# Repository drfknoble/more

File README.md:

# My Other Robot for Education (MORE)

## Introduction

Welcome to my repository for my My Other Robot for Education (MORE) project.

<div>

</div>

## Motivation

I started this project after developing my LORE robot (see [http://github.com/DrFKNoble/lore](http://github.com/DrFKNoble/lore)) and seeing how low-cost components affected the robot's performance.

One of the main problems the robot had was that the continuous rotation servo motors I used would start to "drift" after some time (and would need to be manually tuned when they did). So I decided to build a better robot, which used stepper motors instead on servo motors.

## Aims

The aims of this project included:
- Improving upon LORE's performance by using more robust components.
- Developing another mobile robot that, this time, can be used to teach students the principles of mechatronics and robotics.

## Objectives

The objectives of this project included:
- Creating accessible Computer Aided Design (CAD) files.
- Creating accessible Electronics Design Automation (EDA) files.
- Creating accessible source code and software libraries.
- Creating an easy-to-assemble mobile robot that uses an Arduino microcontroller, stepper motors, stepper motor drives, and ultrasonic sensors.

## Repository Structure

The repository is organised as follows:

```console
/MORE      
    /cad                          
        /solidworks                    
        /freecad
        /fabrication
        /renders                     
    /pcb
        /eagle
        /kicad
        /fabrication
    /src
    /doc                      
        /img
        /programming_guide
```

All CAD files can be found in the `/cad` sub-directory. I've included the original SOLIDWORKS files and the open-source equivalents.

All EDA files can be found in the `/pcb` sub-directory. I've included the original Eagle files and the open-source equivalents.

All source code and software libaries are included in the `/src` sub-directory.

Documentation is included in the `/doc` sub-directory.

## Tools Used

I have used the following tools in this project:
- SOLIDWORKS and FreeCAD.
- Eagle and KiCAD.
- Microsoft Visual Studio and Arduino Integrated Development IDE (IDE).

Get FreeCAD here: https://www.freecadweb.org/.  
Get KiCAD here: https://www.kicad.org/.  
Get Arduino IDE here: https://www.arduino.cc/en/software.  
Get Visual Studio here: https://visualstudio.microsoft.com/.  

Alternatively, you can use Microsoft Visual Studio Code as the IDE.

Get Code here: https://code.visualstudio.com/.

## Credit

Dr Frazer K. Noble  
http://drfknoble.com

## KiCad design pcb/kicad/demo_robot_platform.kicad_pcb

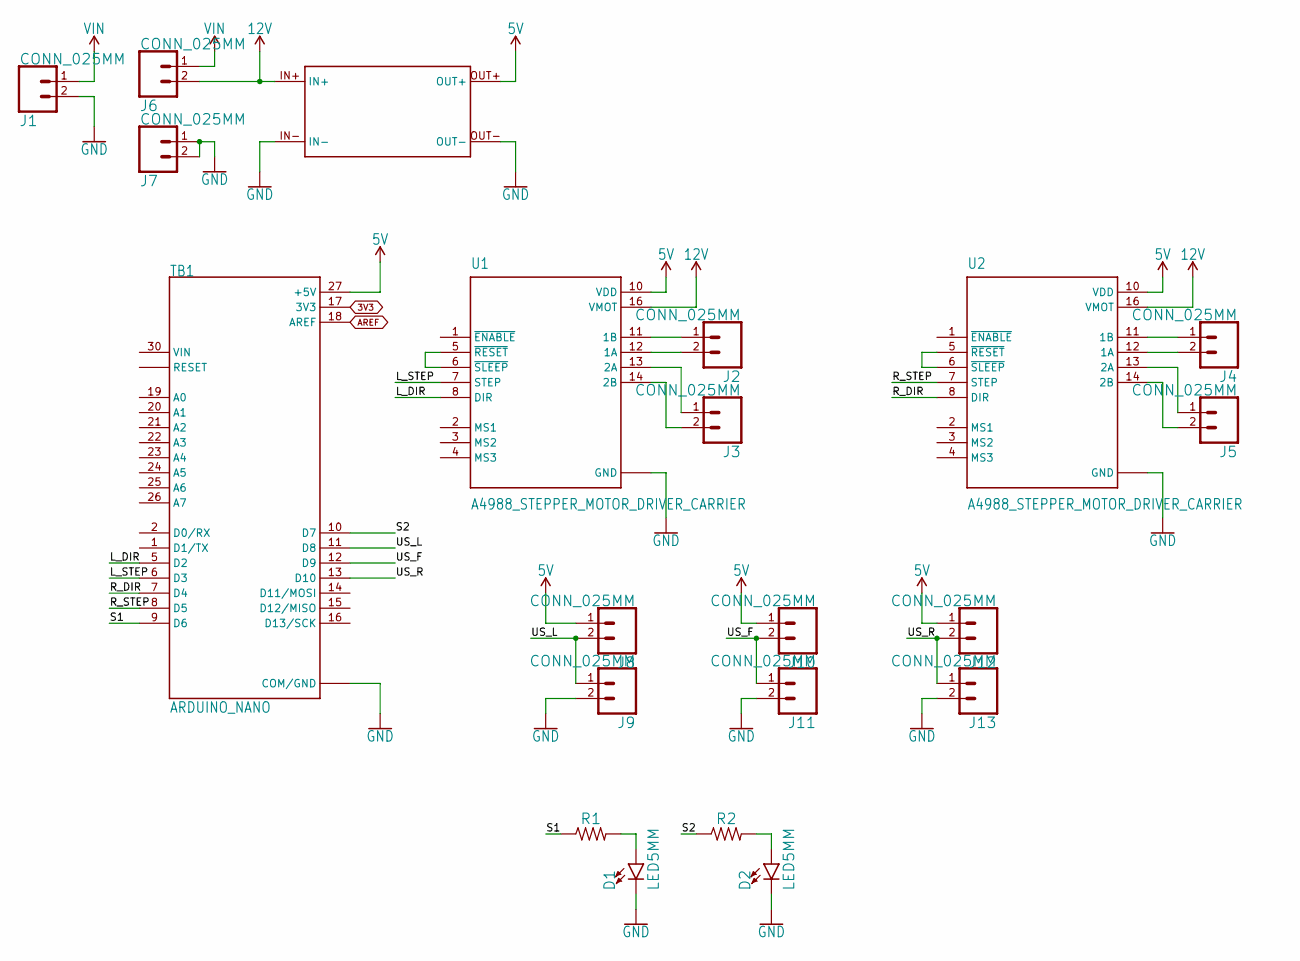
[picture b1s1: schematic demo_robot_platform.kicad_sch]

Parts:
D1, D2: LED5MM; LED_5MM
J1, J2, J3, J4, J5, J6, J7, J8, J9, J10, J11, J12, J13: CONN_025MM; SCREWTERMINAL-5MM-2
R1, R2: AXIAL-0.3
TB1: ARDUINO_NANO; SHIELD_ARDUINO_NANO
U1, U2: A4988_STEPPER_MOTOR_DRIVER_CARRIER; MODULE_A4988_STEPPER_MOTOR_DRIVER_CARRIER
U$1: DC_DC_CONVERTER

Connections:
3V3: TB1.17 (3V3)
5V: J8.1, J10.1, J12.1, TB1.27 (+5V), U1.10 (VDD), U2.10 (VDD), U$1.OUT+
12V: J6.2, U1.16 (VMOT), U2.16 (VMOT), U$1.IN+
AREF: TB1.18 (AREF)
GND: D1.K (C), D2.K (C), J1.2, J7.1, J7.2, J9.2, J11.2, J13.2, TB1.4 (COM/GND), TB1.29 (COM/GND), U1.9 (GND), U1.15 (GND), U2.9 (GND), U2.15 (GND), U$1.IN-, U$1.OUT-
L_DIR: TB1.5 (D2), U1.8 (DIR)
L_STEP: TB1.6 (D3), U1.7 (STEP)
unnamed: J2.1, U1.11 (1B)
unnamed: J2.2, U1.12 (1A)
unnamed: J3.1, U1.13 (2A)
unnamed: J3.2, U1.14 (2B)
unnamed: J4.1, U2.11 (1B)
unnamed: J4.2, U2.12 (1A)
unnamed: J5.1, U2.13 (2A)
unnamed: J5.2, U2.14 (2B)
unnamed: U1.5 (~RESET), U1.6 (~SLEEP)
unnamed: U2.5 (~RESET), U2.6 (~SLEEP)
unnamed: D1.A, R1.P$2 (2)
unnamed: D2.A, R2.P$2 (2)
R_DIR: TB1.7 (D4), U2.8 (DIR)
R_STEP: TB1.8 (D5), U2.7 (STEP)
S1: R1.P$1 (1), TB1.9 (D6)
S2: R2.P$1 (1), TB1.10 (D7)
US_F: J10.2, J11.1, TB1.12 (D9)
US_L: J8.2, J9.1, TB1.11 (D8)
US_R: J12.2, J13.1, TB1.13 (D10)
VIN: J1.1, J6.1

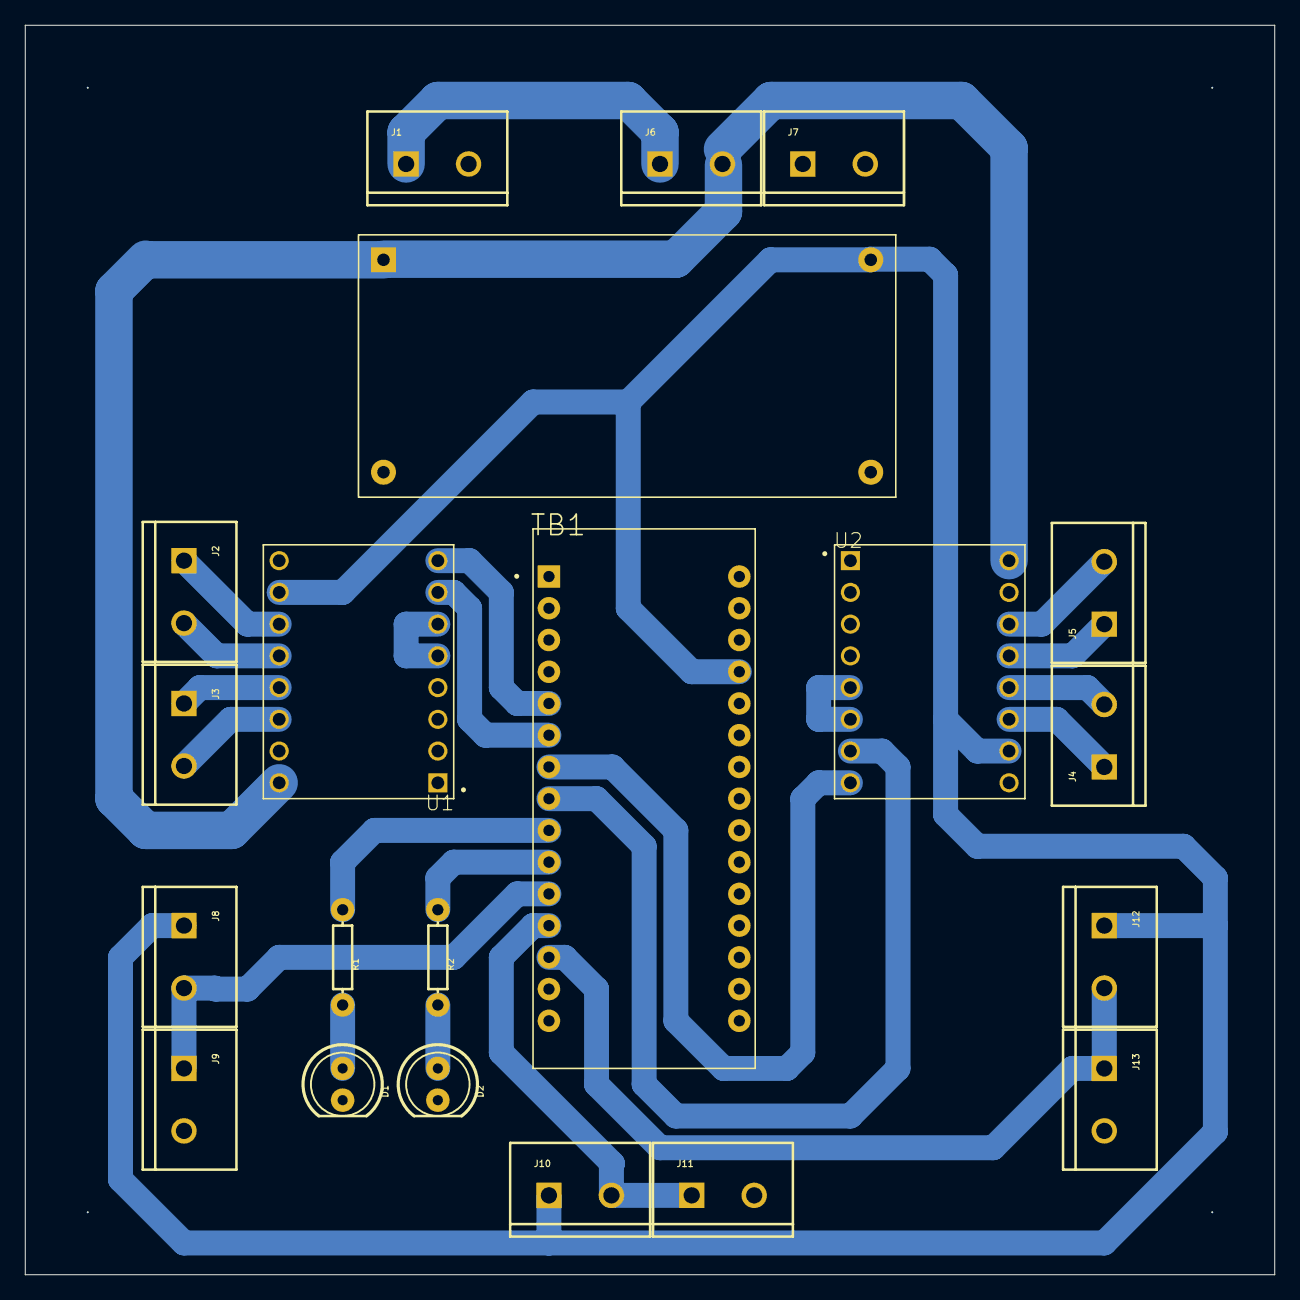
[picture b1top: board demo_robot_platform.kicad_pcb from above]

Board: 2 copper layers, 100.0 x 100.0 mm, 25 parts (0 on the bottom side), 25 nets.

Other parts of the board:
@HOLE0, @HOLE1, @HOLE2, @HOLE3: (no value)

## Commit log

2022-11-02 Tidied up assembly and added open source files.
2022-11-03 Added renders to file.
2022-11-03 Fixed link.
2022-11-07 Added some photos of the real robot.
